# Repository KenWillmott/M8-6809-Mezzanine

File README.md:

# M8-6809-Mezzanine

This board is primarily a companion for the SST-6809 SBC. It adds a timer IC, parallel I/O IC, two UARTs for serial communication. One UART is dedicated to an ESP32 module for wifi and bluetooth communications.

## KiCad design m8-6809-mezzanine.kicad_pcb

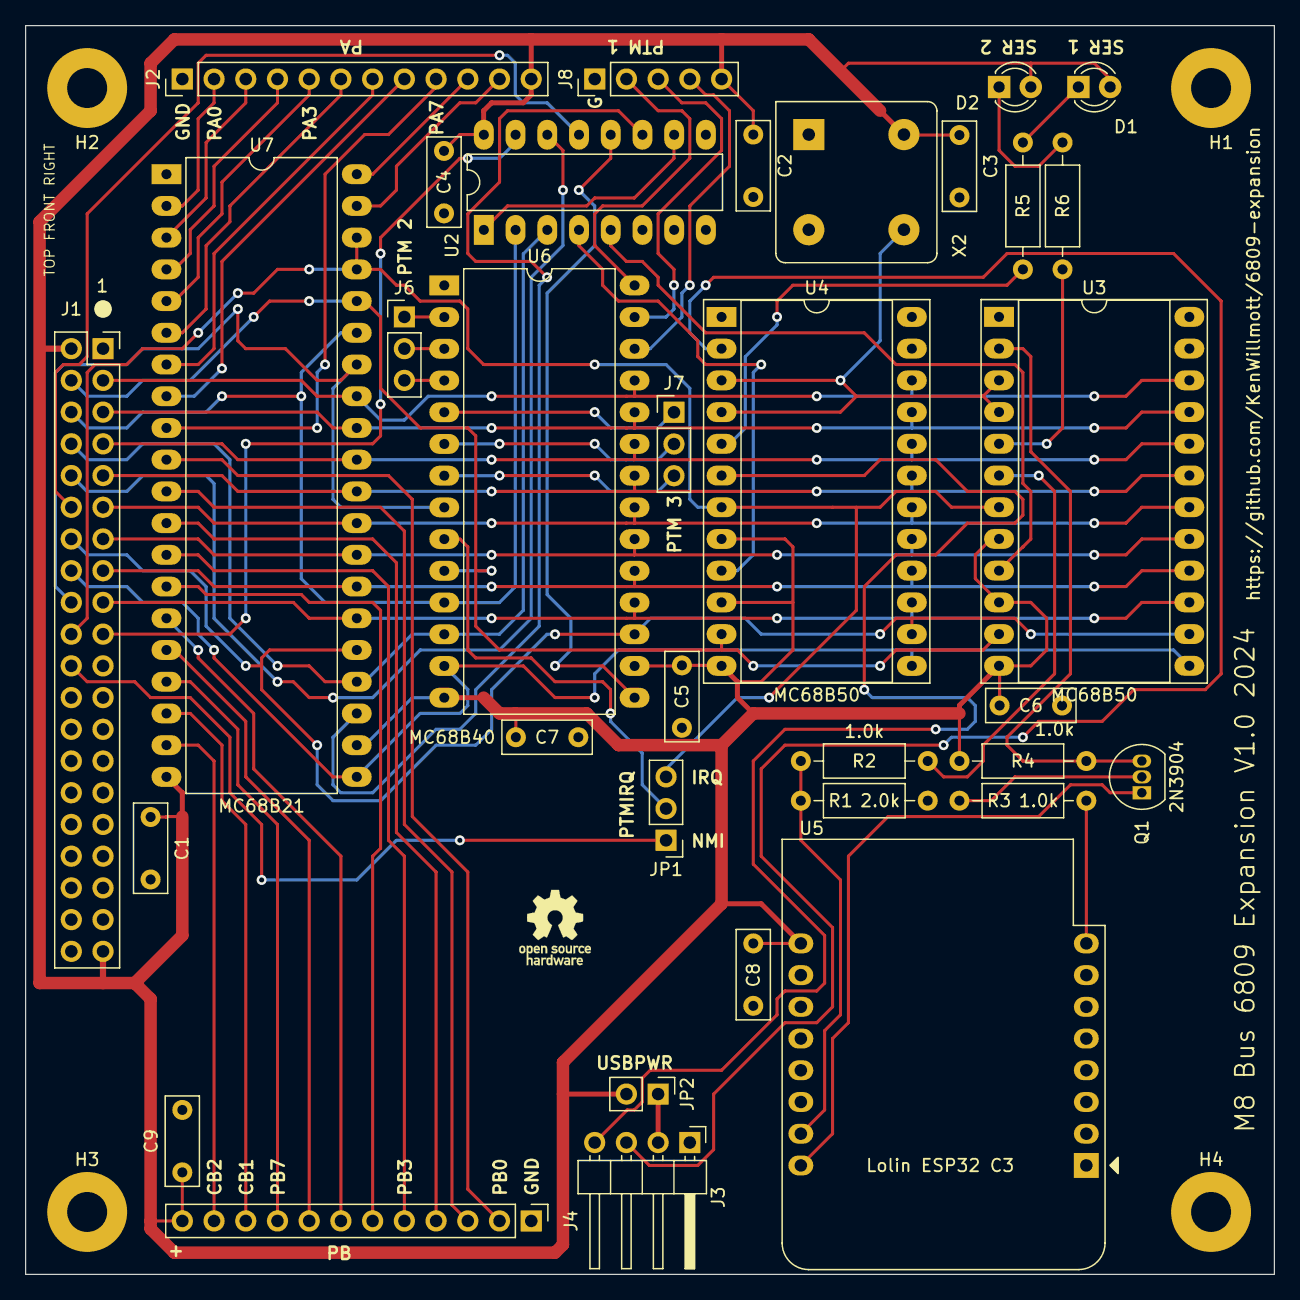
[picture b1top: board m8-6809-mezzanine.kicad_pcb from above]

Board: 2 copper layers, 100.0 x 100.0 mm, 38 parts (0 on the bottom side), 70 nets.

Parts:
C1, C2, C3, C4, C5, C6, C7, C8, C9: 100n; C_Disc_D7.0mm_W2.5mm_P5.00mm
D1, D2: LED; LED_D3.0mm
H1, H2, H3, H4: MountingHole_Pad; MountingHole_3.2mm_M3_Pad
J1: Conn_02x20_Odd_Even; PinSocket_2x20_P2.54mm_Vertical
J2, J4: Conn_01x12_Pin; PinHeader_1x12_P2.54mm_Vertical
J3: Conn_01x04_Pin; PinHeader_1x04_P2.54mm_Horizontal
J6, J7: Conn_01x03_Pin; PinHeader_1x03_P2.54mm_Vertical
J8: Conn_01x05_Pin; PinHeader_1x05_P2.54mm_Vertical
JP1: PTIRQ; PinHeader_1x03_P2.54mm_Vertical
JP2: Jumper_2_Bridged; PinHeader_1x02_P2.54mm_Vertical
Q1: 2N3904; TO-92_Inline
R1: 2.0k; R_Axial_DIN0207_L6.3mm_D2.5mm_P10.16mm_Horizontal
R2, R3, R4, R5, R6: 1.0k; R_Axial_DIN0207_L6.3mm_D2.5mm_P10.16mm_Horizontal
U2: 74LS139; DIP-16_W7.62mm_LongPads
U3, U4: MC68B50; DIP-24_W15.24mm_Socket_LongPads
U5: Lolin ESP32 C3; WEMOS_D1_mini_light
U6: MC68B40; DIP-28_W15.24mm_LongPads
U7: MC68B21; DIP-40_W15.24mm_LongPads
X2: 1.8432M; Oscillator_DIP-8_LargePads

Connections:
/A0: J1.4, U3.11 (RS), U4.11 (RS), U6.10 (RS0), U7.36 (RS0)
/A1: J1.6, U2.2 (A0), U6.11 (RS1), U7.35 (RS1)
/A2: J1.8, U2.3 (A1), U6.12 (RS2), U7.24 (CS1)
/A3: J1.10, U2.14 (A0)
/A4: J1.12, U2.13 (A1)
/D0: J1.3, U3.22 (D0), U4.22 (D0), U6.25 (D0), U7.33 (D0)
/D1: J1.5, U3.21 (D1), U4.21 (D1), U6.24 (D1), U7.32 (D1)
/D2: J1.7, U3.20 (D2), U4.20 (D2), U6.23 (D2), U7.31 (D2)
/D3: J1.9, U3.19 (D3), U4.19 (D3), U6.22 (D3), U7.30 (D3)
/D4: J1.11, U3.18 (D4), U4.18 (D4), U6.21 (D4), U7.29 (D4)
/D5: J1.13, U3.17 (D5), U4.17 (D5), U6.20 (D5), U7.28 (D5)
/D6: J1.15, U3.16 (D6), U4.16 (D6), U6.19 (D6), U7.27 (D6)
/D7: J1.17, U3.15 (D7), U4.15 (D7), U6.18 (D7), U7.26 (D7)
/E: J1.14, U3.14 (E), U4.14 (E), U6.17 (ENABLE), U7.25 (ENABLE)
/IRQ*: J1.20, JP1.3 (B), U3.7 (~IRQ), U4.7 (~IRQ), U7.37 (~IRQB), U7.38 (~IRQA)
/PA0: J2.2, U7.2 (PA0)
/PA7: J2.9, U7.9 (PA7)
/PB0: J4.2, U7.10 (PB0)
/PB7: J4.9, U7.17 (PB7)
/RES*: J1.18, U6.8 (~RESET), U7.34 (~RESET)
/R/W*: J1.16, U3.13 (R/~W), U4.13 (R/~W), U6.13 (R/~W), U7.21 (R/~W)
/bus/NMI: J1.22, JP1.1 (A)
BSEL0*: J1.19, U2.15 (E)
GND: C1.2, C2.2, C3.2, C4.2, C5.2, C6.2, C7.2, C8.2, C9.2, H1.1, H2.1, H3.1, H4.1, J1.1, J1.40, J2.1, J3.1, J4.1, J8.1, R1.2, U2.8 (GND), U3.1 (VSS), U3.23 (~DCD), U3.24 (~CTS), U4.1 (VSS), U4.23 (~DCD), U4.24 (~CTS), U5.10 (GND), U6.1 (VSS), U7.1 (VSS), X2.4 (GND)
unnamed: D1.1 (K), R5.1
unnamed: D2.1 (K), R6.1
unnamed: J2.3, U7.3 (PA1)
unnamed: J2.4, U7.4 (PA2)
unnamed: J2.5, U7.5 (PA3)
unnamed: J2.6, U7.6 (PA4)
unnamed: J2.7, U7.7 (PA5)
unnamed: J2.8, U7.8 (PA6)
unnamed: J2.10, U7.40 (CA1)
unnamed: J2.11, U7.39 (CA2)
unnamed: J3.2, JP2.1 (A)
unnamed: J3.3, U4.2 (Rx_Data)
unnamed: J3.4, U4.6 (Tx_Data)
unnamed: J4.3, U7.11 (PB1)
unnamed: J4.4, U7.12 (PB2)
unnamed: J4.5, U7.13 (PB3)
unnamed: J4.6, U7.14 (PB4)
unnamed: J4.7, U7.15 (PB5)
unnamed: J4.8, U7.16 (PB6)
unnamed: J4.10, U7.18 (CB1)
unnamed: J4.11, U7.19 (CB2)
unnamed: J6.1, U6.2 (~G2)
unnamed: J6.2, U6.3 (O2)
unnamed: J6.3, U6.4 (~C2)
unnamed: J7.1, U6.5 (~G3)
unnamed: J7.2, U6.6 (O3)
unnamed: J7.3, U6.7 (~C3)
unnamed: J8.2, U6.28 (~C1)
unnamed: J8.3, U6.27 (O1)
unnamed: J8.4, U6.26 (~G1)
unnamed: JP1.2 (C), U6.9 (~IRQ)
unnamed: Q1.2 (B), R3.2
unnamed: Q1.3 (C), R4.2, U3.2 (Rx_Data)
unnamed: Q1.1 (E), U5.16 (TX)
unnamed: U2.1 (E), U2.10 (O2)
unnamed: U2.4 (O0), U4.9 (CS2)
unnamed: U2.5 (O1), U3.9 (CS2)
unnamed: U3.3 (Rx_CLK), U3.4 (Tx_CLK), U4.3 (Rx_CLK), U4.4 (Tx_CLK), X2.5 (OUT)
unnamed: R2.1, U3.6 (Tx_Data)
unnamed: R6.2, U3.5 (~RTS)
unnamed: R5.2, U4.5 (~RTS)
unnamed: R3.1, U5.8 (3V3)
unnamed: R1.1, R2.2, U5.15 (RX)
PIASEL*: U2.11 (O1), U7.23 (~CS2)
PTMSEL*: U2.12 (O0), U6.15 (~CS0)
VCC: C1.1, C2.1, C3.1, C4.1, C5.1, C6.1, C7.1, C8.1, C9.1, D1.2 (A), D2.2 (A), J1.2, J1.39, J2.12, J4.12, J8.5, JP2.2 (B), R4.1, U2.16 (VCC), U3.8 (CS0), U3.10 (CS1), U3.12 (VCC), U4.8 (CS0), U4.10 (CS1), U4.12 (VCC), U5.9 (5V), U6.14 (VCC), U6.16 (CS1), U7.20 (VCC), U7.22 (CS0), X2.8 (Vcc)
